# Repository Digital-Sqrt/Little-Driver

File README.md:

# Little-Driver is covered by the Creative Commons Attribution-ShareAlike 3.0 Unported License.
please see the LICENSE test file for more information.

DOC -  All documents for construction, Manufacture, and use of the Little Driver.

Gerbrer -  all files necessary for board manufacturer.

MyLib.pretty - KiCad lib for the little Driver

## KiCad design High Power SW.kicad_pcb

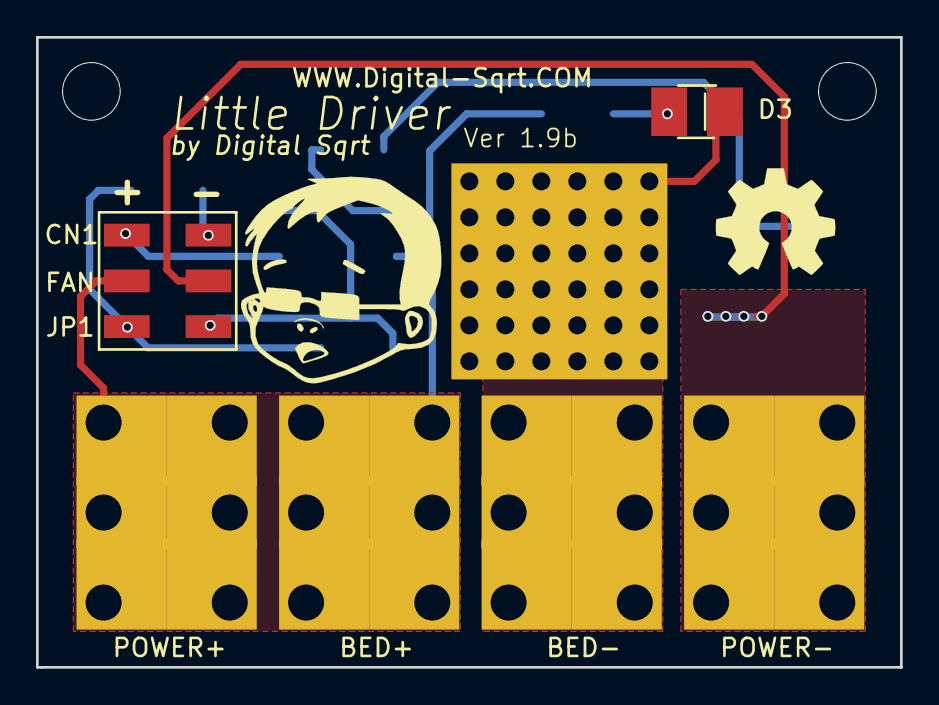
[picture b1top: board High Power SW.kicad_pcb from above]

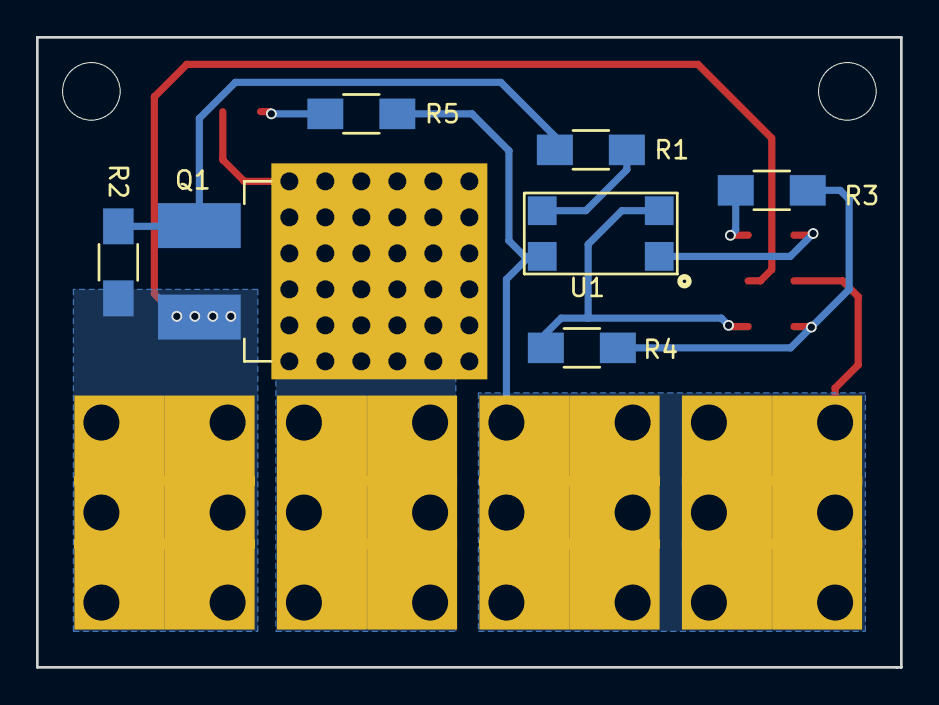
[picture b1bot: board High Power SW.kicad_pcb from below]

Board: 2 copper layers, 48.0 x 35.0 mm, 13 parts (7 on the bottom side), 10 nets.

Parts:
BED+: CONN_01X01; Keystone_terminal
BED-: CONN_01X01; Keystone_terminal
CN1: Jumper_NC_Small; 6pin_SMT_HEADER
D3: Led_Small; CREE_CLM1B_AKW_CUAVB253
POWER+: CONN_01X01; Keystone_terminal
POWER-: CONN_01X01; Keystone_terminal
Q1: IRFR7540TRPBF; TO-263-2Lead_(Small_Heat_Sink)
R1: 1.0K; R_1206_HandSoldering
R2: 1.8K; R_1206_HandSoldering
R3: 300; R_1206_HandSoldering
R4: 1.69K; R_1206_HandSoldering
R5: 3.6K; R_1206_HandSoldering
U1: PS2801C-1-A; TLP182

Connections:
+BATT: BED+.1, CN1.3, POWER+.1, R5.1, U1.6
GND: CN1.4, POWER-.1, Q1.3, R2.2
unnamed: BED-.1, D3.1, Q1.2, Q1.4
unnamed: CN1.1, U1.1
unnamed: CN1.2, R3.1
unnamed: D3.2, R5.2
unnamed: CN1.6, R4.2, U1.3
unnamed: CN1.5, R3.2, R4.1
unnamed: Q1.1, R1.2, R2.1
unnamed: R1.1, U1.4

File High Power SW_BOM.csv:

Reference,Value,Footprint,Count,Datasheet,FootprintLib,mfr_num,Manufacturer,Supplyer,Supplyer_Link,Supplyer_Part_No,Reel_Part_No,Parts_Per_Reel,Cost
R4,1.69K,R_1206_HandSoldering,1,http://www.yageo.com/NewPortal/yageodocoutput?fileName=/pdf/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,Resistors_SMD,RC1206FR-071K69L,Yageo,Digi-Key,http://www.digikey.com/product-detail/en/yageo/RC1206FR-071K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,311-1.69KFRCT-ND,311-1.69KFRTR-ND,5000,.1
R3,300,R_1206_HandSoldering,1,http://www.yageo.com/NewPortal/yageodocoutput?fileName=/pdf/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,Resistors_SMD,RC1206JR-07300RL,Yageo,Digi-Key,http://www.digikey.com/product-detail/en/yageo/RC1206JR-0730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,311-300ERCT-ND,311-300ERTR-ND,5000,.1
U1,PS2801C-1-A,SOP-4,1,"http://www.cel.com/pdf/datasheets/PS2801C-1,PS2801C-4.pdf",MyLib,PS2801C-1-A,CEL,Digi-Key,http://www.digikey.com/product-search/en?keywords=PS2801C-1-A,PS2801C-1-A-ND,PS2801C-1-F3-ATR-ND,3500,
R1,1.0K,R_1206_HandSoldering,1,http://www.yageo.com/NewPortal/yageodocoutput?fileName=/pdf/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,Resistors_SMD,RC1206FR-071KL,Yageo,Digi-Key,http://www.digikey.com/product-detail/en/yageo/RC1206FR-071K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,311-1.00KFRCT-ND,311-1.00KFRTR-ND,5000,.1
D3,Led_Small,CREE_CLM1B_AKW_CUAVB253,1,http://www.cree.com/~/media/Files/Cree/LED%20Components%20an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,MyLib,CLM1B-AKW-CUAVB253,CREE,Digi-Key,http://www.digikey.com/product-search/en?keywords=CLM1B-AKW-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,CLM1B-AKW-CUAVB253CT-ND,CLM1B-AKW-CUAVB253TR-ND,2500,
CN1;FAN1,Jumper_NC_Small,6pin_SMT_HEADER,2,http://www.molex.com/pdm_docs/sd/015912060_sd.pdf,MyLib,0015912060,"Molex, LLC",Digi-Key,http://www.digikey.com/product-detail/en/molex-llc/001591206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,WM17449-ND,,6600,
JP1,Jumper_NC_Small,Cut_Jumper,1,http://multimedia.3m.com/mws/media/548120O/3mtm-shunt-ts2186.pdf,MyLib,969102-0000-DA,3M,Digi-Key,http://www.digikey.com/product-detail/en/3m/969102-0000-DA/3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,3M9580-ND,None,None,
R2,1.8K,R_1206_HandSoldering,1,http://www.yageo.com/NewPortal/yageodocoutput?fileName=/pdf/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,Resistors_SMD,RC1206FR-071K8L,Yageo,Digi-Key,http://www.digikey.com/product-detail/en/yageo/RC1206FR-0724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,311-1.80KFRCT-ND,311-1.80FRTR-ND,5000,.1
R5,3.6K,R_1206_HandSoldering,1,http://www.yageo.com/NewPortal/yageodocoutput?fileName=/pdf/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,Resistors_SMD,RC1206FR-073K6L,Yageo,Digi-Key,http://www.digikey.com/products/en?keywords=311-3.60KFRCT-ND,311-3.60KFRCT-ND,311-3.60FRTR-ND,5000,
POWER-1;POWER+1;BED+1;BED-1,CONN_01X01,Keystone_terminal,4,http://www.keyelco.com/product-pdf.cfm?p=1534,MyLib,8197,Keystone Electronics,Digi-Key,http://www.digikey.com/products/en?keywords=36-8197-ND,36-8197-ND,NA,NA,
Q1,PSMN5R6-60YLX,SOT-669_LFPAK_ThermalVias-2,1,http://cache.nxp.com/documents/data_sheet/PSMN5R6-60YL.pdf,TO_SOT_Packages_SMD,PSMN5R6-60YLX,Nexperia USA Inc.,Digi-Key,http://www.digikey.com/product-detail/en/nexperia-usa-inc/PS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,568-13047-1-ND,568-13047-2-ND,1500,

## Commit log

2017-01-08 Add files via upload
    This is the 1.5v of the boar an the first commit.
2017-01-11 Update to schmatic and BOM
    Updated R1 to 1.0K
    Added mating connector information to schematic
2017-01-11 Bug Fix
    Fixed Ki-Cad BOM generation error
2017-01-18 Add License
    Add Creative Commons Attribution-ShareAlike 3.0 Unported License
2017-01-19 Added Logo's to the schmatic and pcb
    Added a pending OSHWA Pending logo to the board
    Added Digital Sqrt Logo to board
2017-01-19 Added CC ref
    Little Driver is licensed under a
    Creative Commons Attribution-ShareAlike 3.0 Unported License.
2017-02-01 Update Manifacturing Files
2017-02-01 Manufacturing Files
2017-02-01 Updated documentation
2017-02-02 Updated BOM
2017-02-04 Update for KiCost
    Updated Parts Lib so KiCost will work with KiCad
2017-02-04 Clean Up
2017-02-05 Errors found in componet links in schmatic
2017-02-07 Maded Udates to silk
2017-02-10 Updated Board
    Changed connector type
2017-02-11 Update Gerbr files
2017-02-11 Update Gerbers
2017-02-11 Update Gerbers One more time
2017-02-11 Various Small updates
2017-02-12 Update to better parts
    UpDates to better parts for smaller board.
2017-02-12 Improved Board Size
    Made the board smaller
2017-02-12 Reduced Board Size
    Cleaned up the board and made it smaller
2017-02-13 Changed back to orginal connectors
    Changed back to orginal connectors. They are more sturdy.
2017-02-13 Fixed Silk
2017-02-13 Minor Tweeks
2017-02-15 Updated Gerber Files
2017-02-15 Updated Documents
    Updated documents, cleaned up files, added Brackets
2017-02-15 Added Ver 1_5 BOM in PDF
2017-02-16 Added ver 1_5 doc's
2017-02-17 Added BOM for Ver 1.7
2017-02-17 Added win file
2017-02-18 Add Manufacturing Files
2017-02-18 File Clean Up
2017-02-18 Added Build Diagram
2017-02-18 Up Load the last of the Manufacturing files
2017-02-23 Revert "Up Load the last of the Manufacturing files"
    This reverts commit ee7e60682b5b21ff10b9b6b08a1b8972e26ac501.
2017-02-23 Fix a big GIT HUB screw up
2017-02-23 Added OSHWA Number to board
2017-02-24 Grammar checked Manual.
2017-02-28 Updated Manuel
    Fixed spelling errors and Grammar problems
2017-04-01 added more mounting holes
2017-04-01 Generated Gerber Files
2017-04-01 Added Manufacturing Files
2017-04-01 improved hole size and location drawings
2017-04-01 Updated Documents
2017-04-02 Clean Up Folders
2017-04-02 updated Manual
2017-04-02 updated documents for ver 1_8
2017-04-09 Update GERBER and Silk
2017-04-14 Updtes for Manufacture
2017-04-14 Make board 5x5
    5cm by 5cm boards are lower cost
2017-04-14 Update for improved Manufacture
2017-04-20 Improved opto
2017-04-21 Update opto footprint and add logos
2017-04-21 Updated Bracket files for a 50mm Board
2017-04-21 Updating Documentation
2017-04-21 fixed Gerbers
2017-04-22 Cleaned up Folder
2017-04-22 Updated bill of materials
2017-04-22 Update Doc's
2017-04-22 Dupdate DOC's again - dimentions
2017-04-22 clean up folder
2017-04-23 New circuit Documentation
2017-04-25 better picture
2017-04-28 Update Board Design based on feedback
2017-04-28 Cleaned up Gerber Data
2017-05-02 Compleat Redesign
2017-05-03 cleaned up gerber files
2017-05-09 Update gerberf iles
2017-05-11 Fixed issues with manufacture
2017-05-13 Fixed Buggs found in Prototypes
2017-05-14 Updates to Brackets
2017-05-21 Update documentation
2017-05-21 Add BOM
2017-05-29 fixed issue with the links
2017-06-24 Add Bill of Materials
2017-11-23 Updated Brackets.
    The fans would hit JP1, they have been moved.
2017-11-23 updated doc
    Updated board Docs
2017-11-23 Update Board for Better FET
2017-11-23 Improve FET Design
    Add new FET
2017-11-23 Documentation Updates
    Documentation Updates
2018-02-25 Fixed error in schmatic
    The opto isolator had the incorrect part number
